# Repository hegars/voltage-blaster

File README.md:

# Voltage Blaster Mod

Voltage Blaster is a very simple circuit, which provides -5V through ISA slot
for systems with power supply which don't provide such voltage. It was originaly created
in cooperation between PhilsComputerLab and Necroware then forked and modified by Hegars.

## Changes From Necroware version

PCB
* Updated - Pulled Mask from ISA Cconnector
* Updated - Pulled Mask from the top of TO-220 package to allow soldering
* Added - Linked copper zone beneath TO-220 package to -12v for soldering 
* Updated - NPTH mount on TO-220 package changed to PTH
* Added - Added Vias under TO-220 for heat transfer to rear copper zone
* Added - Added Copper zone on rear for heat sinking and capacitance (Linked at -12v)
* Updated - Slight components aliginments
* Moved - Logo changed from Silk to Mask and moved credits around
* Updated - Version number
* Updated - PCB corners rounded
* Updated - "PC Rear" locator to make it a bit more clear the direction
* Added - Pin numbers added for relevent pins for refernece
* Removed - Unused Pins on ISA Connector 

SCH
* Updated - Changed to global lables
* Updated - Version number

Many thanks to Necroware and PhilsComputerLab, I owe you some beers..

# Voltage Blaster SMD

In Version 2 I have moved all components to SMD variants

## SMD Changelog 

* Added - SMD version with TO-263-3 package (LM2990S-5.0/NOPB LCSC-C201697)
* Updated - Componets to SMD variants
* Added - PTC Fuses on both power rails
* Added - Mounting hole for reasons
* Added - Test Points on rear for science
* Added - LED for -12v rail
* Moved - Logo and credits to rear
* Updated - Verison numbers
* Add? - Minimum load resistor?

## SMD BOM

Reference  |#  |LCSC   |Description
-----------|---|-------|-------------------------------------
U1         | 1 |C201697| linear voltage regulator
C1,C2      | 2 |C88824 | electrolytic capacitor 33µF
F1         | 1 |C692148| fuse
F2         | 1 |C692149| fuse
D1         | 1 |C192678| light emitting diode
D2         | 1 |C192674| light emitting diode
R1,R2      | 1 |C269588| resistor

# Original Voltage Blaster Description

## Why do I need this?

Back in the days of XT and AT compatible computers the standard power supply had
to provide 5V, 12V, -12V and -5V. A lot of hardware, especially sound cards,
needed -5V to work properly. This voltage was provided for the ISA expansion
cards on the pin B5. As time passed, AT systems and compatible power supplies
were replaced by ATX. In the beginning they also provided -5V, but then less and
less expansion cards needed such voltage and as soon as ISA was considered 
obsolete, ATX standard eventually dropped -5V rail requirement. Today it is not
possible to buy a new AT power supply, but ATX power supplies can be used
through an adapter. However, since almost none of the modern ATX power supplies
will provide -5V, you could run into problems, when trying to use an old ISA
expansion card, which needs this voltage. Famous examples are Creative Sound
Blaster 2.0, Pro Audio Spectrum sound cards and many others. This is where the
Voltage Blaster comes into play.

## How does it work?

All voltage pins in the ISA slots are directly connected to each other and to
the PSU. When using a PSU without -5V support, the ISA slot pin B5 is just
floating. The idea behind the Voltage Blaster is very simple. What if one of the
ISA expansion cards will provide -5V and feed it through the ISA slot in
reverse. Well since the ISA slot pin B7 provides -12V, it's just a matter of
using a linear voltage regulator LM7905 and connect its output to the pin B5 of
the ISA slot.

## Bill of materials

Reference  |#  |LCSC   |Description
-----------|---|-------|-------------------------------------
U1         | 1 |C427634| linear voltage regulator LM7905
C1,C2      | 2 |C3314  | electrolytic capacitor 33µF
D1         | 1 |C99697 | light emitting diode (optional)
R1         | 1 |C58608 | resistor 330 Ohm (optional)

Parts D1 and R1 are optional and are only required if you want that the diode is
lighting, when -5V are generated.

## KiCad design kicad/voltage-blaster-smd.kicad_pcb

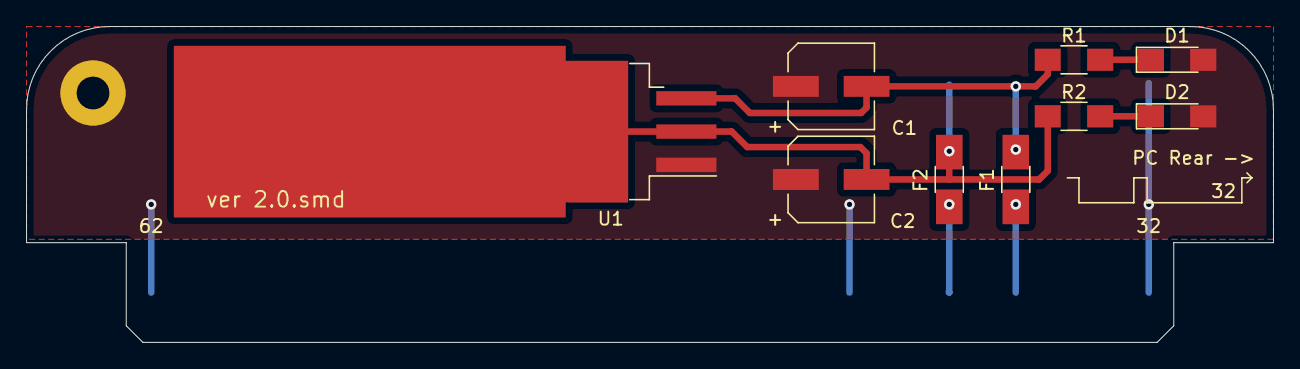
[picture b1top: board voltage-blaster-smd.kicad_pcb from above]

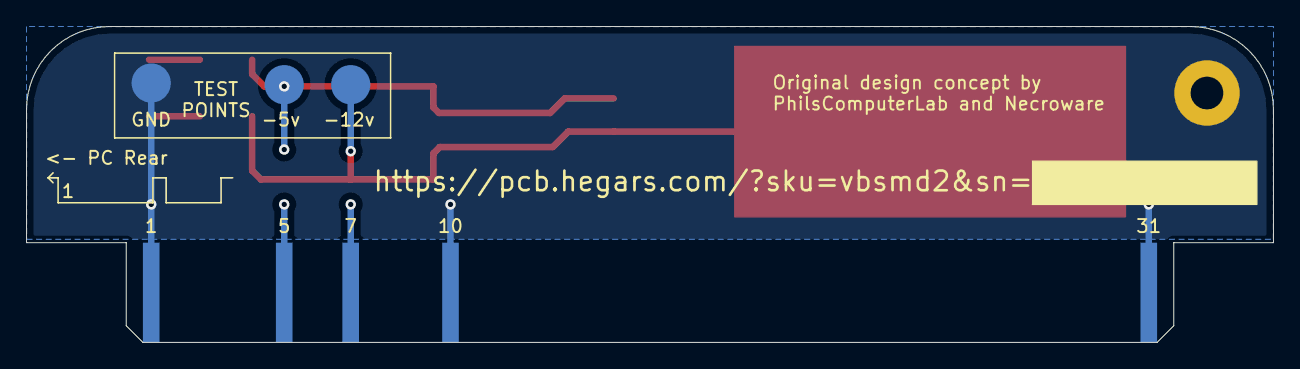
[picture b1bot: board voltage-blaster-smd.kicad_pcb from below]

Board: 2 copper layers, 95.2 x 24.1 mm, 14 parts (3 on the bottom side), 5 nets.

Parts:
C1, C2: 33u; CP_Elec_6.3x5.7
D1: -5V; LED_1206_HandSoldering
D2: -12V; LED_1206_HandSoldering
F1, F2: Fuse; Fuse_SMD1206_HandSoldering
H1: MountingHole_Pad; MountingHole_2.5mm_Pad
J1: Bus_ISA_8bit; ISA_8BIT_EDGE_voltageblaster
R1, R2: 330; R_1206_HandSoldering
TP1, TP2, TP3: TestPoint; Measurement_Point_Round-SMD-Pad_Big
U1: LM7905; TO-263-3_TabPin2

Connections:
-5V: C1.2, F1.2, J1.5, R1.1, TP1.1, U1.3
-12V: C2.2, F2.2, J1.7, R2.1, TP2.1, U1.2
GND: C1.1, C2.1, D1.2, D2.2, H1.1, J1.1, J1.10, J1.31, TP3.1, U1.1
unnamed: D1.1, R1.2
unnamed: D2.1, R2.2

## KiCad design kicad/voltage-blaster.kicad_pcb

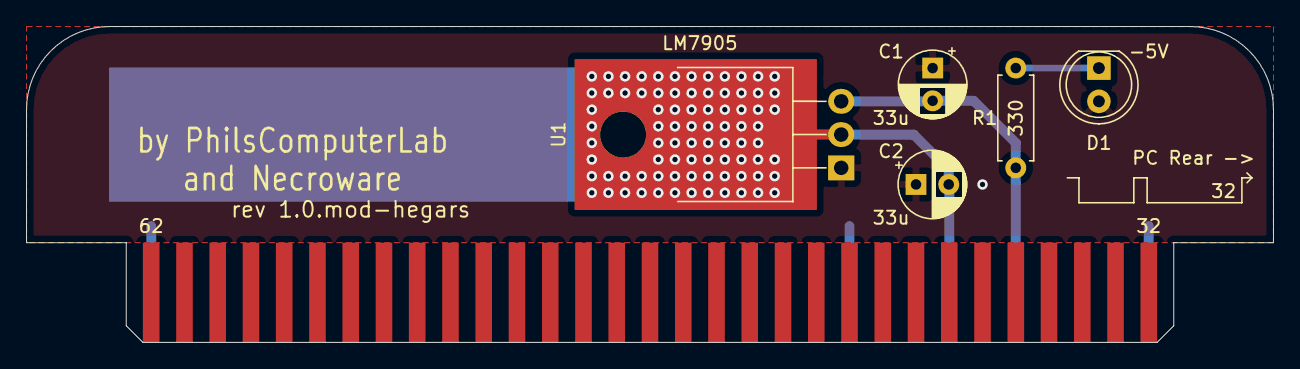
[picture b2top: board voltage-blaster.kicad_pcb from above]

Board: 2 copper layers, 95.2 x 24.1 mm, 6 parts (0 on the bottom side), 4 nets.

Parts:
C1, C2: 33u; CP_Radial_D5.0mm_P2.50mm
D1: -5V; LED_D5.0mm
J1: Bus_ISA_8bit; ISA_8BIT_EDGE
R1: 330; R_Axial_DIN0207_L6.3mm_D2.5mm_P7.62mm_Horizontal
U1: LM7905; TO-220-3_Horizontal_TabDown

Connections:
-5V: C1.2, J1.5, R1.1, U1.3
-12V: C2.2, J1.7, U1.2
GND: C1.1, C2.1, D1.2, J1.1, J1.10, J1.31, U1.1
unnamed: D1.1, R1.2

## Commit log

2021-02-24 no pins mod
2021-02-24 updated for nopins
2021-03-22 added prod board images
2021-03-27 Added SMD variant
2021-03-27 update images
2021-03-27 remove from root
2021-03-29 image updates
